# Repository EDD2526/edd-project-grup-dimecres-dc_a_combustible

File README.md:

View this project on [CADLAB.io](https://cadlab.io/project/30189). 

# Projecte Combustible

>**Autors:** David Puges & Victor Donet
>**Versió: ** v.1.0.0 11/03/2026

----------

*3D render of the Fuel Management Electronic Module designed in KiCad 9. 
The board integrates a PIC24HJ128GP502 microcontroller, CAN bus (MCP2562), 
RS232 (MAX3232), 12-bit I2C DAC (MCP4725), two 12V/6A power relays and a 
complete power management stage (buck LM2596 + LDO LM1117).*

----------
## Objectiu Descripció breu de l'objectiu del projecte.

L'objectiu del projecte és crear una pcb capaç de controlar el mecanisme de tancament de dipòsit del combustible d'un cotxe, controli el sensor de pressió de pneumàtics i el sensor digital de nivell de combustible i el funcionament de la bomba de combustible.

## Diagrama de blocs

-----------

## Requisits / Especificacions

  - Una etapa regulador de tensió per alimentar tots el components de la placa.
  - Tenir un microcontrolador encarregat del control de la nostra placa.
  - Tenir una connexió BUS CAN, I2C.
  - Una comuniació USART per connectar el microcontrolador a aparells extern ja ve sigui un ordinador.
  - Tenir entrades com un boto per a que s'interección amb la placa.

-----------

## Components

| Descripci&#243; | Ref | Package |Datasheet | Prove&#239;dor | Unitats |
| --- | --- | --- | --- | --- | --- |
| Microcontrolador | PIC24HJ128GP502 | SOIC-28 |[Datasheet](https://ww1.microchip.com/downloads/aemDocuments/documents/OTH/ProductDocuments/DataSheets/70293G.pdf) | Mouser| 1x |
| XTAL-Ressonador | X49SM8MSD2SC | SMD |[Datasheet](https://www.lcsc.com/datasheet/C326536.pdf?spm=wm.sxq.inf.ggs___wm.ssy.bg.1.xh&lcsc_vid=QgJYBQUFQwQLBQFXFFAPUVFUTlMLX1dREgBeXgEFFlAxVlNRQFVfX1RVQVBdUDsOAxUeFF5JWBYZEEoKFBINSQcJGk4%3D) | [LCSC] | 1x |
| Regulador de tensió        | LM1117            | SOT-223 | [Enllaç](https://www.ti.com/lit/ds/symlink/lm1117.pdf) | Mouser | 1 |
| Regulador de commutació    | LM2596            | TO-220 / TO-263 | [Enllaç](https://www.ti.com/lit/ds/symlink/lm2596.pdf) |Mouser | 1 |
| Transceptor CAN            | MCP2557           | SOIC-8  | [Enllaç](https://www.digikey.es/es/products/detail/microchip-technology/MCP2557FD-H-SN/6009299?gclsrc=aw.ds&&utm_adgroup=&utm_source=google&utm_medium=cpc&utm_campaign=PMax_Product_All%20Products&utm_term=&productid=6009299&utm_content=&utm_id=go_cmp-20199915072_adg-_ad-__dev-c_ext-_prd-6009299_sig-Cj0KCQjw_JzABhC2ARIsAPe3ynpUKI6YB1CwYhuxLEUHioMMJoSxuswcCzv73NbuUfjEhpO7h3KmzM0aAg-ZEALw_wcB&gad_source=1&gbraid=0AAAAADrbLli4DwHuL2SABBDwoZRf1ZzGQ&gclid=Cj0KCQjw_JzABhC2ARIsAPe3ynpUKI6YB1CwYhuxLEUHioMMJoSxuswcCzv73NbuUfjEhpO7h3KmzM0aAg-ZEALw_wcB&gclsrc=aw.ds) | DigiKey | 1 |
| Convertidor DAC            | MCP4725           | SOT-23-6 | [Enllaç](https://ww1.microchip.com/downloads/en/devicedoc/22039d.pdf) | DigiKey / Mouser | 1 |
| Relé | Fujitsu_FTR-LYAA005Y | SPST-Vertical | [Enllaç](https://www.fujitsu.com/sg/imagesgig5/ftr-ly.pdf) | Mouser | 2 |
| Díode protector | PMEG6030EP | Diode_SMD:D_SOD-128 | [Enllaç](https://www.vishay.com/docs/88516/1n5400.pdf) | Mouser | 2 |
| Pulsador reset | SKRKAEE020 | SW_Push_SPST_NO_Alps_SKRK | [Enllaç](https://www.mouser.es/datasheet/2/15/SKRK-1370789.pdf) | Mouser | 1 |
| Connector DB9 | DB9 PINS | DSUB-9 THT | [Enllaç](https://www.we-online.com/components/products/datasheet/61800925123.pdf?srsltid=AfmBOoq6FDOjEsmwkl3Im1lC_McuY10mhKZld1XstQI9LiwjvFeB6EgA) | Digikey | 1 |
| Connector 01x02 | 61300211121 | PinHeader_1x02_P2.54mm_Vertical | [Enllaç](https://www.we-online.com/components/products/datasheet/61300211121.pdf) |Digikey | 4 |
| Connector ISCP | 61200621621 | PinHeader_2x03_P2.54mm_Vertical | [Enllaç](https://www.we-online.com/components/products/datasheet/61200621621.pdf) | Digikey | 1 |
| Connector Usart | 61300611121 | PinHeader_1x06_P2.54mm_Vertical | [Enllaç](https://www.we-online.com/components/products/datasheet/61300611121.pdf) | Digikey | 1 |
-----------

### Eines:

  * KiCad 9.0 o superior 

### Funcionalitats:

  - El mecanisme de tancament i obertura del dipòsit de combustible
  - Un sensor digital del nivell de combustible
  - El mecanisme que controli la bomba de combustible
  - Un sensor que ens avisi quan la pressió dels pneumàtics sigui baixa 

-----------

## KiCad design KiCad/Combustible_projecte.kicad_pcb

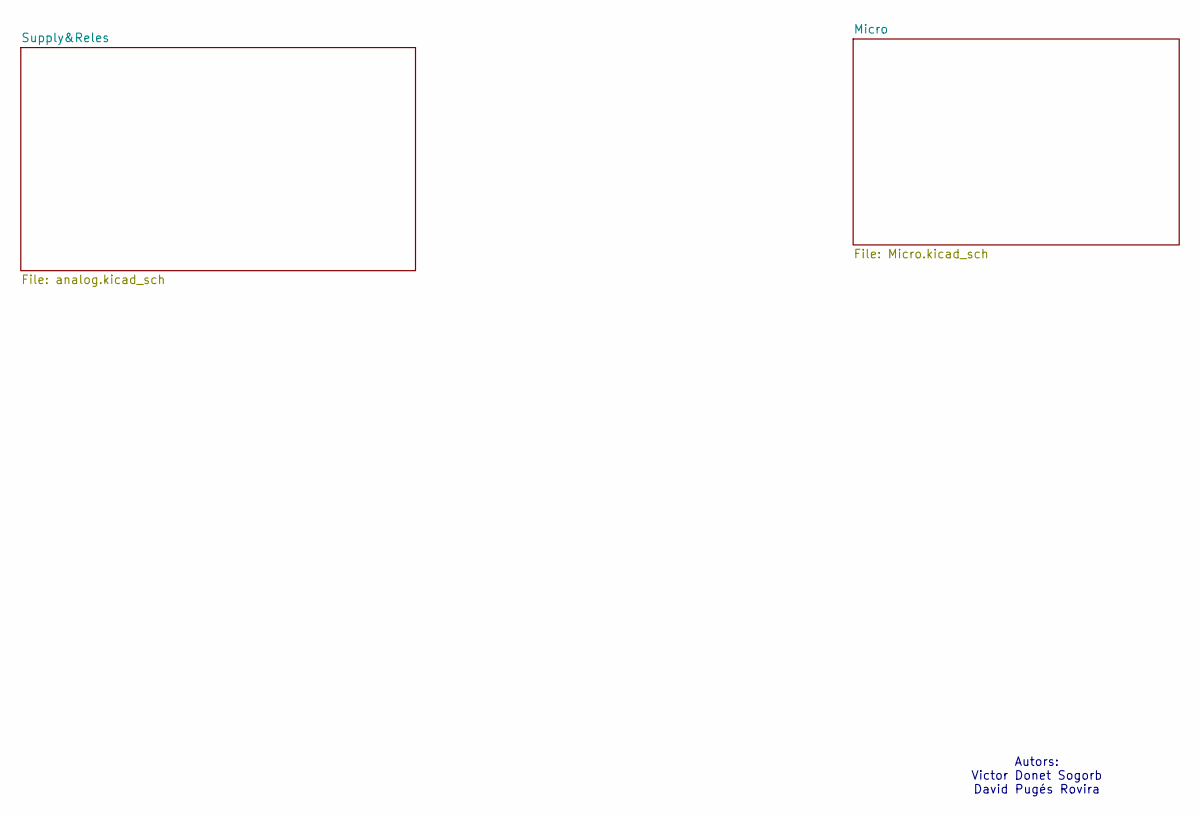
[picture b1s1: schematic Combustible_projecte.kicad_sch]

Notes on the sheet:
Autors: Victor Donet Sogorb David Pugés Rovira

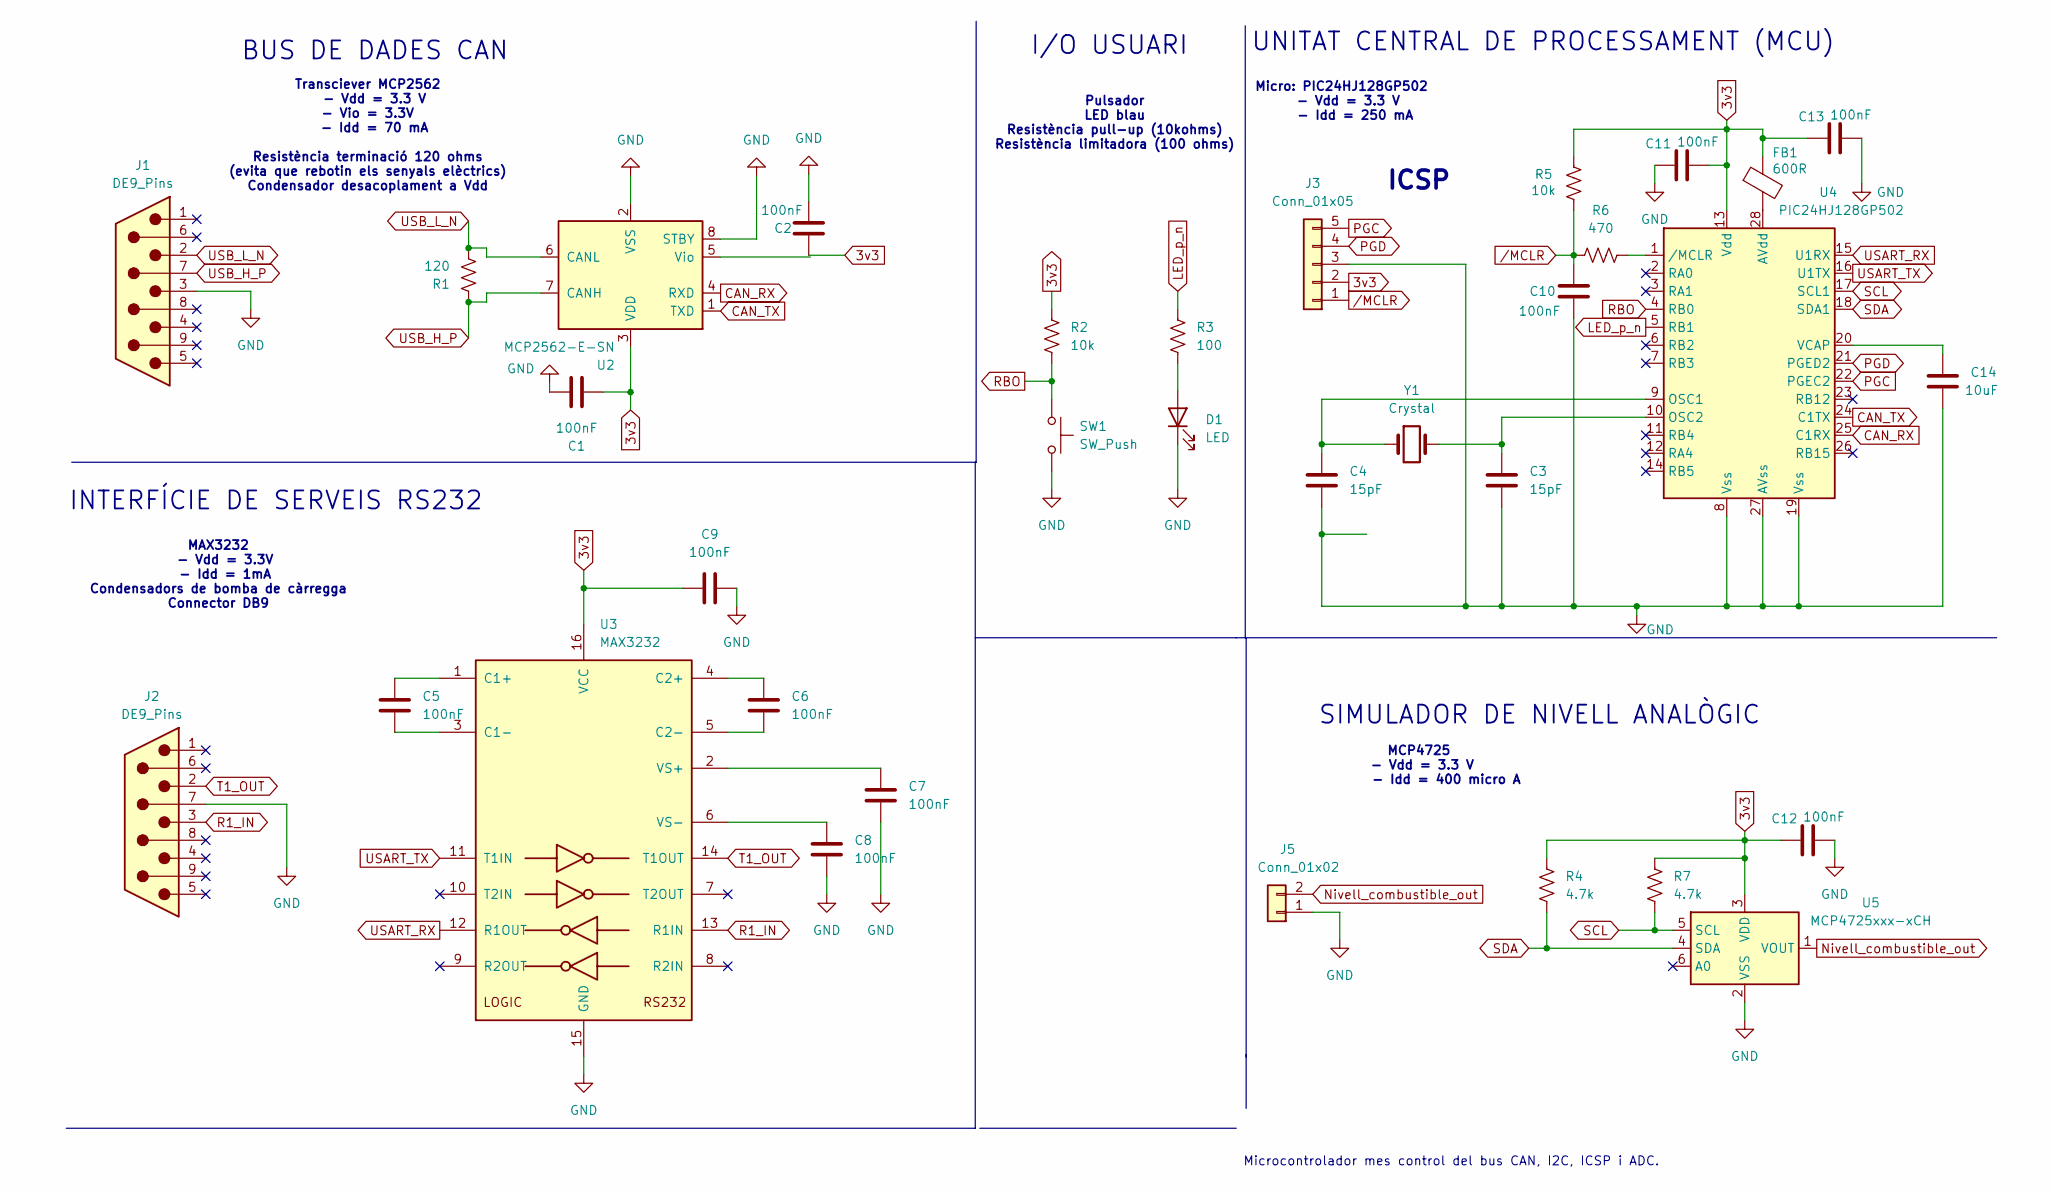
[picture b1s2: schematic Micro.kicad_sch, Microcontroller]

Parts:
C1, C2, C5, C6, C7, C8, C9, C10, C11, C12, C13: 100nF; C_1206_3216Metric
C3, C4: 15pF; C_0805_2012Metric
C14: 10uF; CP_EIA-3528-12_Kemet-T
D1: LED; LED_0805_2012Metric
FB1: 600R; R_1206_3216Metric
J1, J2: DE9_Pins; DSUB-9_Pins_Horizontal_P2.77x2.84mm_EdgePinOffset4.94mm_Hou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
J3: Conn_01x05; TerminalBlock_TE_282834-5_1x05_P2.54mm_Horizontal
J5: Conn_01x02; TerminalBlock_TE_282834-2_1x02_P2.54mm_Horizontal
R1: 120; R_1206_3216Metric
R2, R5: 10k; R_1206_3216Metric
R3: 100; R_1206_3216Metric
R4, R7: 4.7k; R_1206_3216Metric
R6: 470; R_1206_3216Metric
SW1: SW_Push; SW_Push_SPST_NO_Alps_SKRK
U2: MCP2562-E-SN; SOIC-8_3.9x4.9mm_P1.27mm
U3: MAX3232; SOIC-16_3.9x9.9mm_P1.27mm
U4: PIC24HJ128GP502; SOIC-28W_7.5x17.9mm_P1.27mm
U5: MCP4725xxx-xCH; SOT-23-6
Y1: Crystal; Crystal_HC49-U_Vertical

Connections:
3v3: C1.1, C2.2, C9.1, C11.2, C12.1, C13.1, FB1.1, J3.2, R2.1, R4.1, R5.2, R7.1, U2.3 (VDD), U2.5 (Vio), U3.16 (VCC), U4.13 (Vdd), U5.3 (VDD); also elsewhere on the board
CAN_H: J1.7, R1.1, U2.7 (CANH)
CAN_L: J1.2, R1.2, U2.6 (CANL)
CAN_RX: U2.4 (RXD), U4.25 (C1RX)
CAN_TX: U2.1 (TXD), U4.24 (C1TX)
GND: C1.2, C2.1, C3.2, C4.2, C7.2, C8.2, C9.2, C10.1, C11.1, C12.2, C13.2, C14.2, D1.1 (K), J1.3, J2.7, J3.3, J5.1, SW1.2, U2.2 (VSS), U2.8 (STBY), U3.15 (GND), U4.8 (Vss), U4.19 (Vss), U4.27 (AVss), U5.2 (VSS); also elsewhere on the board
LED_p_n: R3.1, U4.5 (RB1)
unnamed: D1.2 (A), R3.2
unnamed: C5.1, U3.1 (C1+)
unnamed: C5.2, U3.3 (C1-)
unnamed: C6.1, U3.4 (C2+)
unnamed: C6.2, U3.5 (C2-)
unnamed: C7.1, U3.2 (VS+)
unnamed: C8.1, U3.6 (VS-)
unnamed: FB1.2, U4.28 (AVdd)
unnamed: C4.1, U4.9 (OSC1), Y1.1
unnamed: C3.1, U4.10 (OSC2), Y1.2
unnamed: C14.1, U4.20 (VCAP)
unnamed: R6.2, U4.1 (/MCLR)
Nivell_combustible_out: J5.2, U5.1 (VOUT)
PGC: J3.5, U4.22 (PGEC2)
PGD: J3.4, U4.21 (PGED2)
R1_IN: J2.3, U3.13 (R1IN)
RBO: R2.2, SW1.1, U4.4 (RB0)
SCL: R7.2, U4.17 (SCL1), U5.5 (SCL)
SDA: R4.2, U4.18 (SDA1), U5.4 (SDA)
T1_OUT: J2.2, U3.14 (T1OUT)
USART_RX: U3.12 (R1OUT), U4.15 (U1RX)
USART_TX: U3.11 (T1IN), U4.16 (U1TX)
/MCLR: C10.2, J3.1, R5.1, R6.1

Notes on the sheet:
I/O USUARI
BUS DE DADES CAN
UNITAT CENTRAL DE PROCESSAMENT (MCU)
MAX3232 - Vdd = 3.3V - Idd = 1mA Condensadors de bomba de càrregga Connector DB9
Microcontrolador mes control del bus CAN, I2C, ICSP i ADC.
MCP4725 - Vdd = 3.3 V - Idd = 400 micro A
Transciever MCP2562 - Vdd = 3.3 V - Vio = 3.3V - Idd = 70 mA Resistència terminació 120 ohms (evita que rebotin els senyals elèctrics) Condensador desacoplament a Vdd
SIMULADOR DE NIVELL ANALÒGIC
Micro: PIC24HJ128GP502 - Vdd = 3.3 V - Idd = 250 mA
ICSP
INTERFÍCIE DE SERVEIS RS232
Pulsador LED blau Resistència pull-up (10kohms) Resistència limitadora (100 ohms)

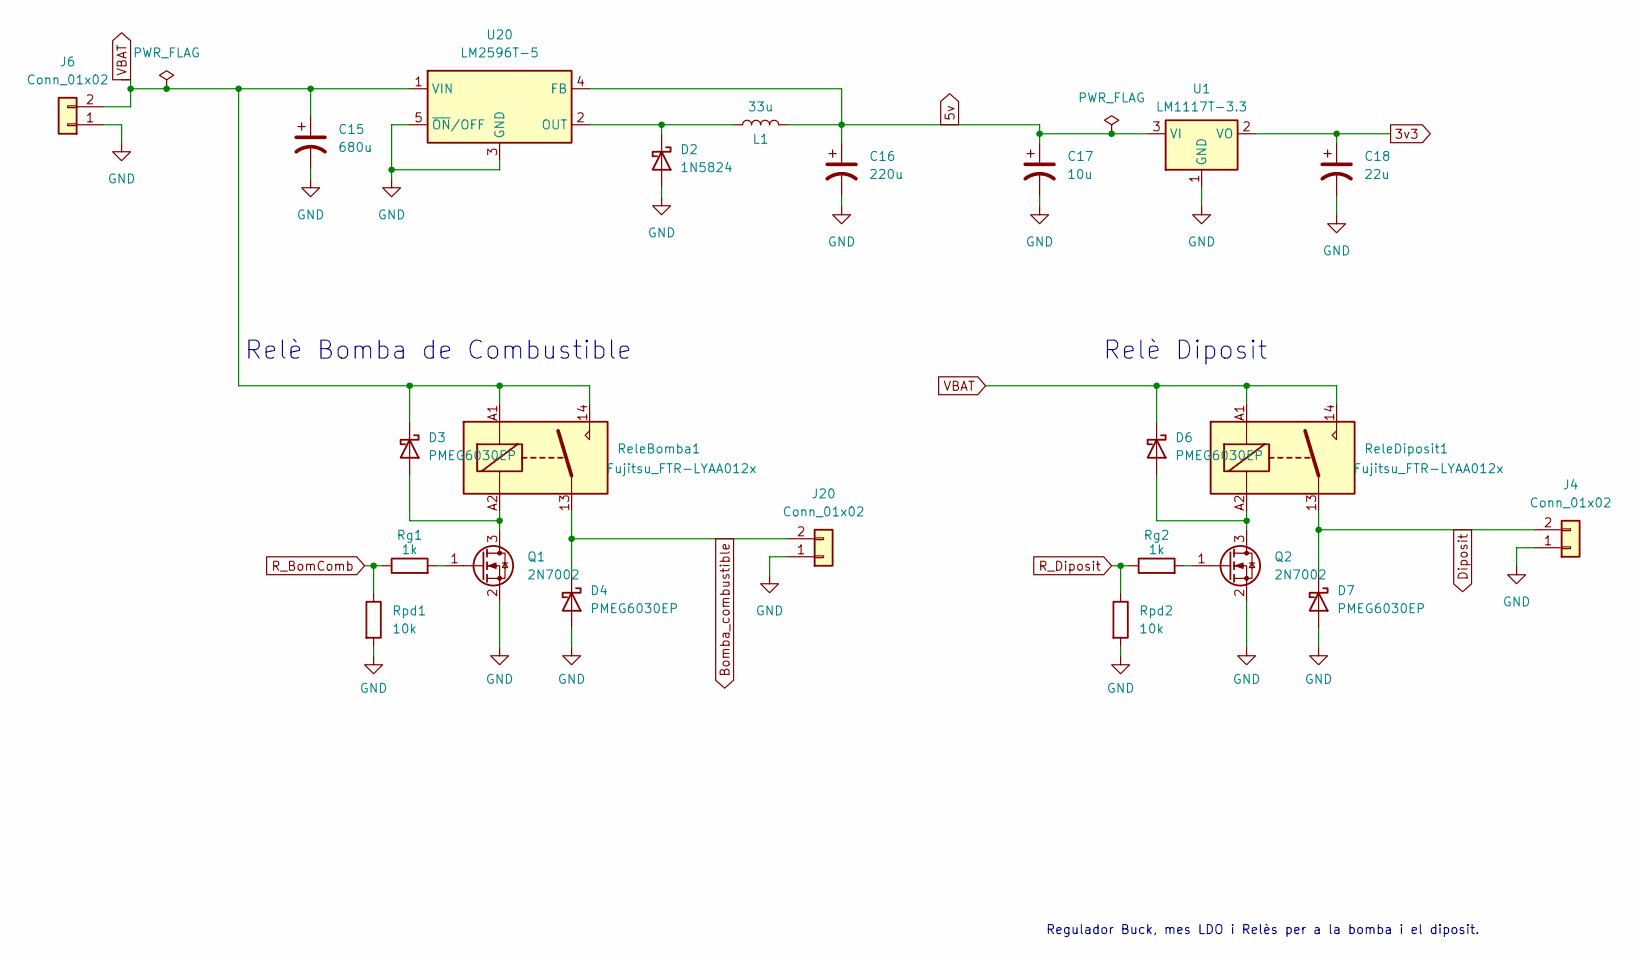
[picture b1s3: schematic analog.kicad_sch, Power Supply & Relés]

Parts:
C15: 680u; CP_Elec_10x10
C16: 220u; CP_Elec_10x10
C17: 10u; CP_EIA-3528-12_Kemet-T
C18: 22u; CP_EIA-3216-12_Kemet-S
D2: 1N5824; D_DO-201AD_P15.24mm_Horizontal
D3, D4, D6, D7: PMEG6030EP; D_SOD-128
J4, J6, J20: Conn_01x02; TerminalBlock_TE_282834-2_1x02_P2.54mm_Horizontal
L1: 33u; L_1206_3216Metric
Q1, Q2: 2N7002; SOT-23
ReleBomba1: Fujitsu_FTR-LYAA012x; Relay_SPST-NO_Fujitsu_FTR-LYAA005x_FormA_Vertical
ReleDiposit1: Fujitsu_FTR-LYAA012x; Relay_SPST-NO_Fujitsu_FTR-LYAA005x_FormA_Vertical
Rg1, Rg2: 1k; R_1206_3216Metric
Rpd1, Rpd2: 10k; R_1206_3216Metric
U1: LM1117T-3.3; TO-220-3_Horizontal_TabDown
U20: LM2596T-5; TO-220-5_P3.4x3.7mm_StaggerOdd_Lead3.8mm_Vertical

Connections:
3v3: C18.1, U1.2 (VO); also elsewhere on the board
5v: C16.1, C17.1, L1.2, U1.3 (VI), U20.4 (FB)
Bomba_combustible: D4.1 (K), J20.2, ReleBomba1.13
Diposit: D7.1 (K), J4.2, ReleDiposit1.13
GND: C15.2, C16.2, C17.2, C18.2, D2.2 (A), D4.2 (A), D7.2 (A), J4.1, J6.1, J20.1, Q1.2 (S), Q2.2 (S), Rpd1.2, Rpd2.2, U1.1 (GND), U20.3 (GND), U20.5 (~ON/OFF); also elsewhere on the board
unnamed: D2.1 (K), L1.1, U20.2 (OUT)
unnamed: D3.2 (A), Q1.3 (D), ReleBomba1.A2
unnamed: D6.2 (A), Q2.3 (D), ReleDiposit1.A2
unnamed: Q1.1 (G), Rg1.2
unnamed: Q2.1 (G), Rg2.2
R_BomComb: Rg1.1, Rpd1.1
R_Diposit: Rg2.1, Rpd2.1
VBAT: C15.1, D3.1 (K), D6.1 (K), J6.2, ReleBomba1.14, ReleBomba1.A1, ReleDiposit1.14, ReleDiposit1.A1, U20.1 (VIN)

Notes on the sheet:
Relè Bomba de Combustible
Regulador Buck, mes LDO i Relès per a la bomba i el diposit.
Relè Diposit

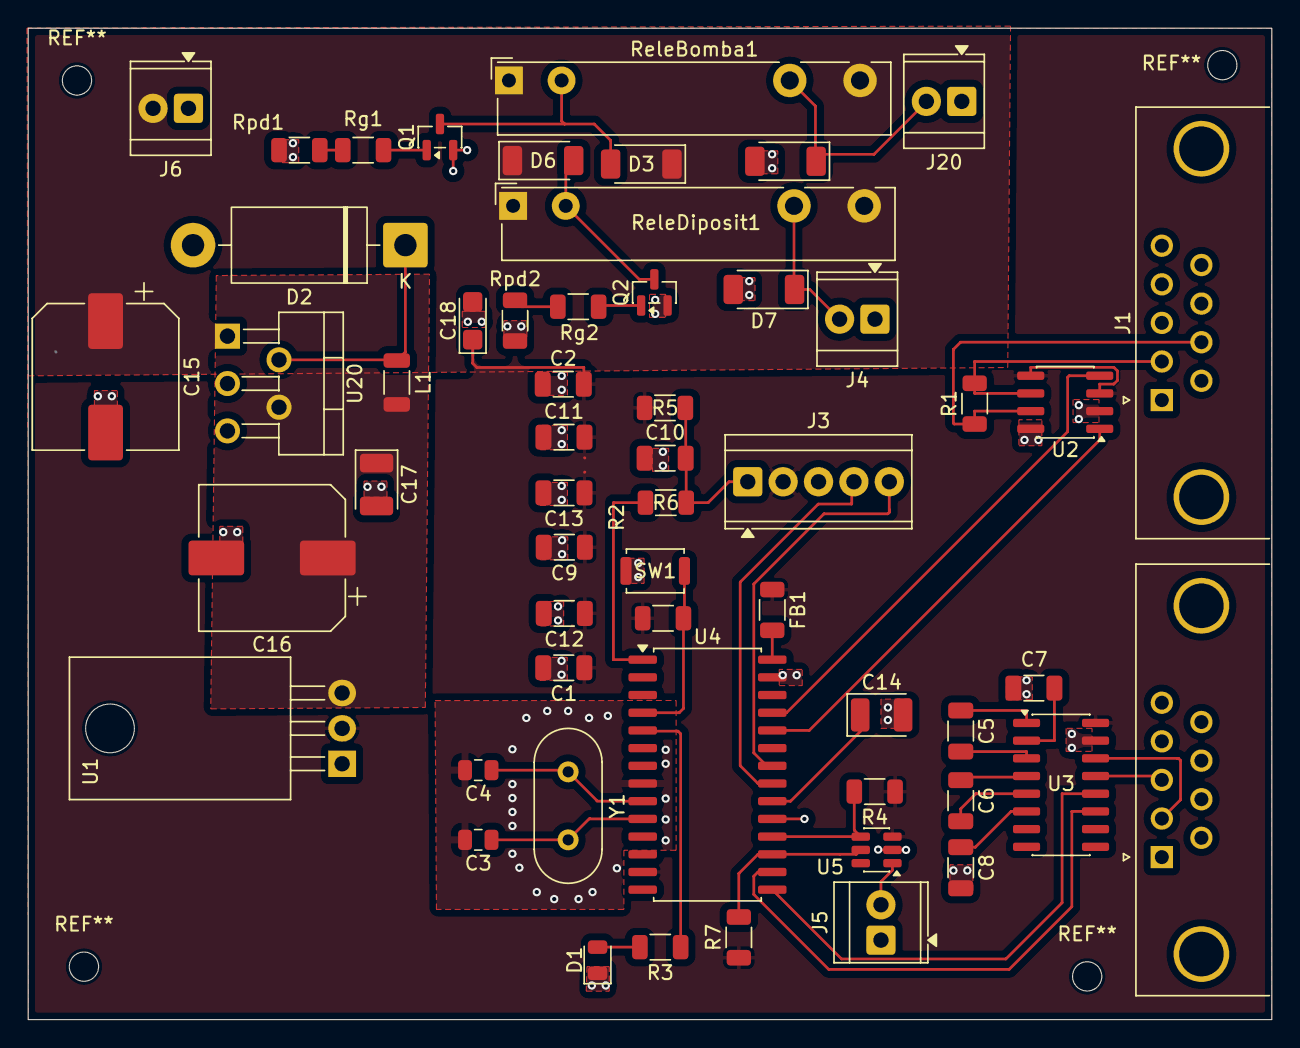
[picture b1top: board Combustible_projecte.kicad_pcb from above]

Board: 2 copper layers, 89.2 x 71.2 mm, 56 parts (0 on the bottom side), 41 nets.

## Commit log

2026-03-11 autors afegits al readme
2026-03-11 projecte kicad creat
2026-03-11 dibuix micro creat
2026-03-11 Especificat el model de micro
2026-03-16 Afegit el micro i les etapes del bus CAN i USART, també afegit el cristall i el debug
2026-03-16 Backlink to CADLAB.io has been added.
2026-03-17 Afegit el micro, el bus CAN i el USART
2026-03-17 Feta la part digital del micro
2026-03-17 Afegida l'etapa digital i el micro
2026-03-17 Part Analogica i Buck fet, falta regulador LDO lineal
2026-03-17 millora etapa micro
2026-03-17 Regulador LDO fet, part analogica finalitzada
2026-03-17 millora micro
2026-03-17 neteja de fitxers temporals de kicad
2026-03-17 millora disseny micro
2026-03-17 Part de potencia acabada, concretar certs pins del micro
2026-03-18 Arreglat els pins i cambiat el model del relé
2026-03-21 canvi del micro i millora
2026-03-21 micro canviat i millorat
2026-03-24 Part de potencia moguda al sheet de analogica, esborrat el sheet de potencia
2026-03-24 Errores ERC corregidos, instanciaciones arregladas
2026-03-24 millora del micro
2026-03-24 canvi d'etiquetes
2026-03-25 Sheets nombrades amb titol, i part del supply millorada
2026-03-25 readme editat amb objectius i en teoria imatge
2026-03-25 sheets editades
2026-04-05 Totes les footprints seleccionades, part de potencia, placement realitzat
2026-04-06 Actualització fitxers kicad
2026-04-07 PnR Final versió 1
2026-04-07 PnR Final versió 2, VBAT i 5V afegit
2026-04-07 pista de 5 volts incluida
2026-04-08 pnr editat
2026-04-12 millora routing
2026-04-14 millora pcb
2026-04-14 millora illa de coure a gnd
2026-04-15 millora vies gnd
2026-04-15 pcb bastant canviada i actualitzada
2026-04-24 Rotuing acabat? falta les regles del fabricant
2026-04-29 Ultims canvis i completat el README
2026-04-29 arreglar l'error del README
2026-04-29 arreglar l'error del README v2
2026-04-29 arreglar l'error del README v3
